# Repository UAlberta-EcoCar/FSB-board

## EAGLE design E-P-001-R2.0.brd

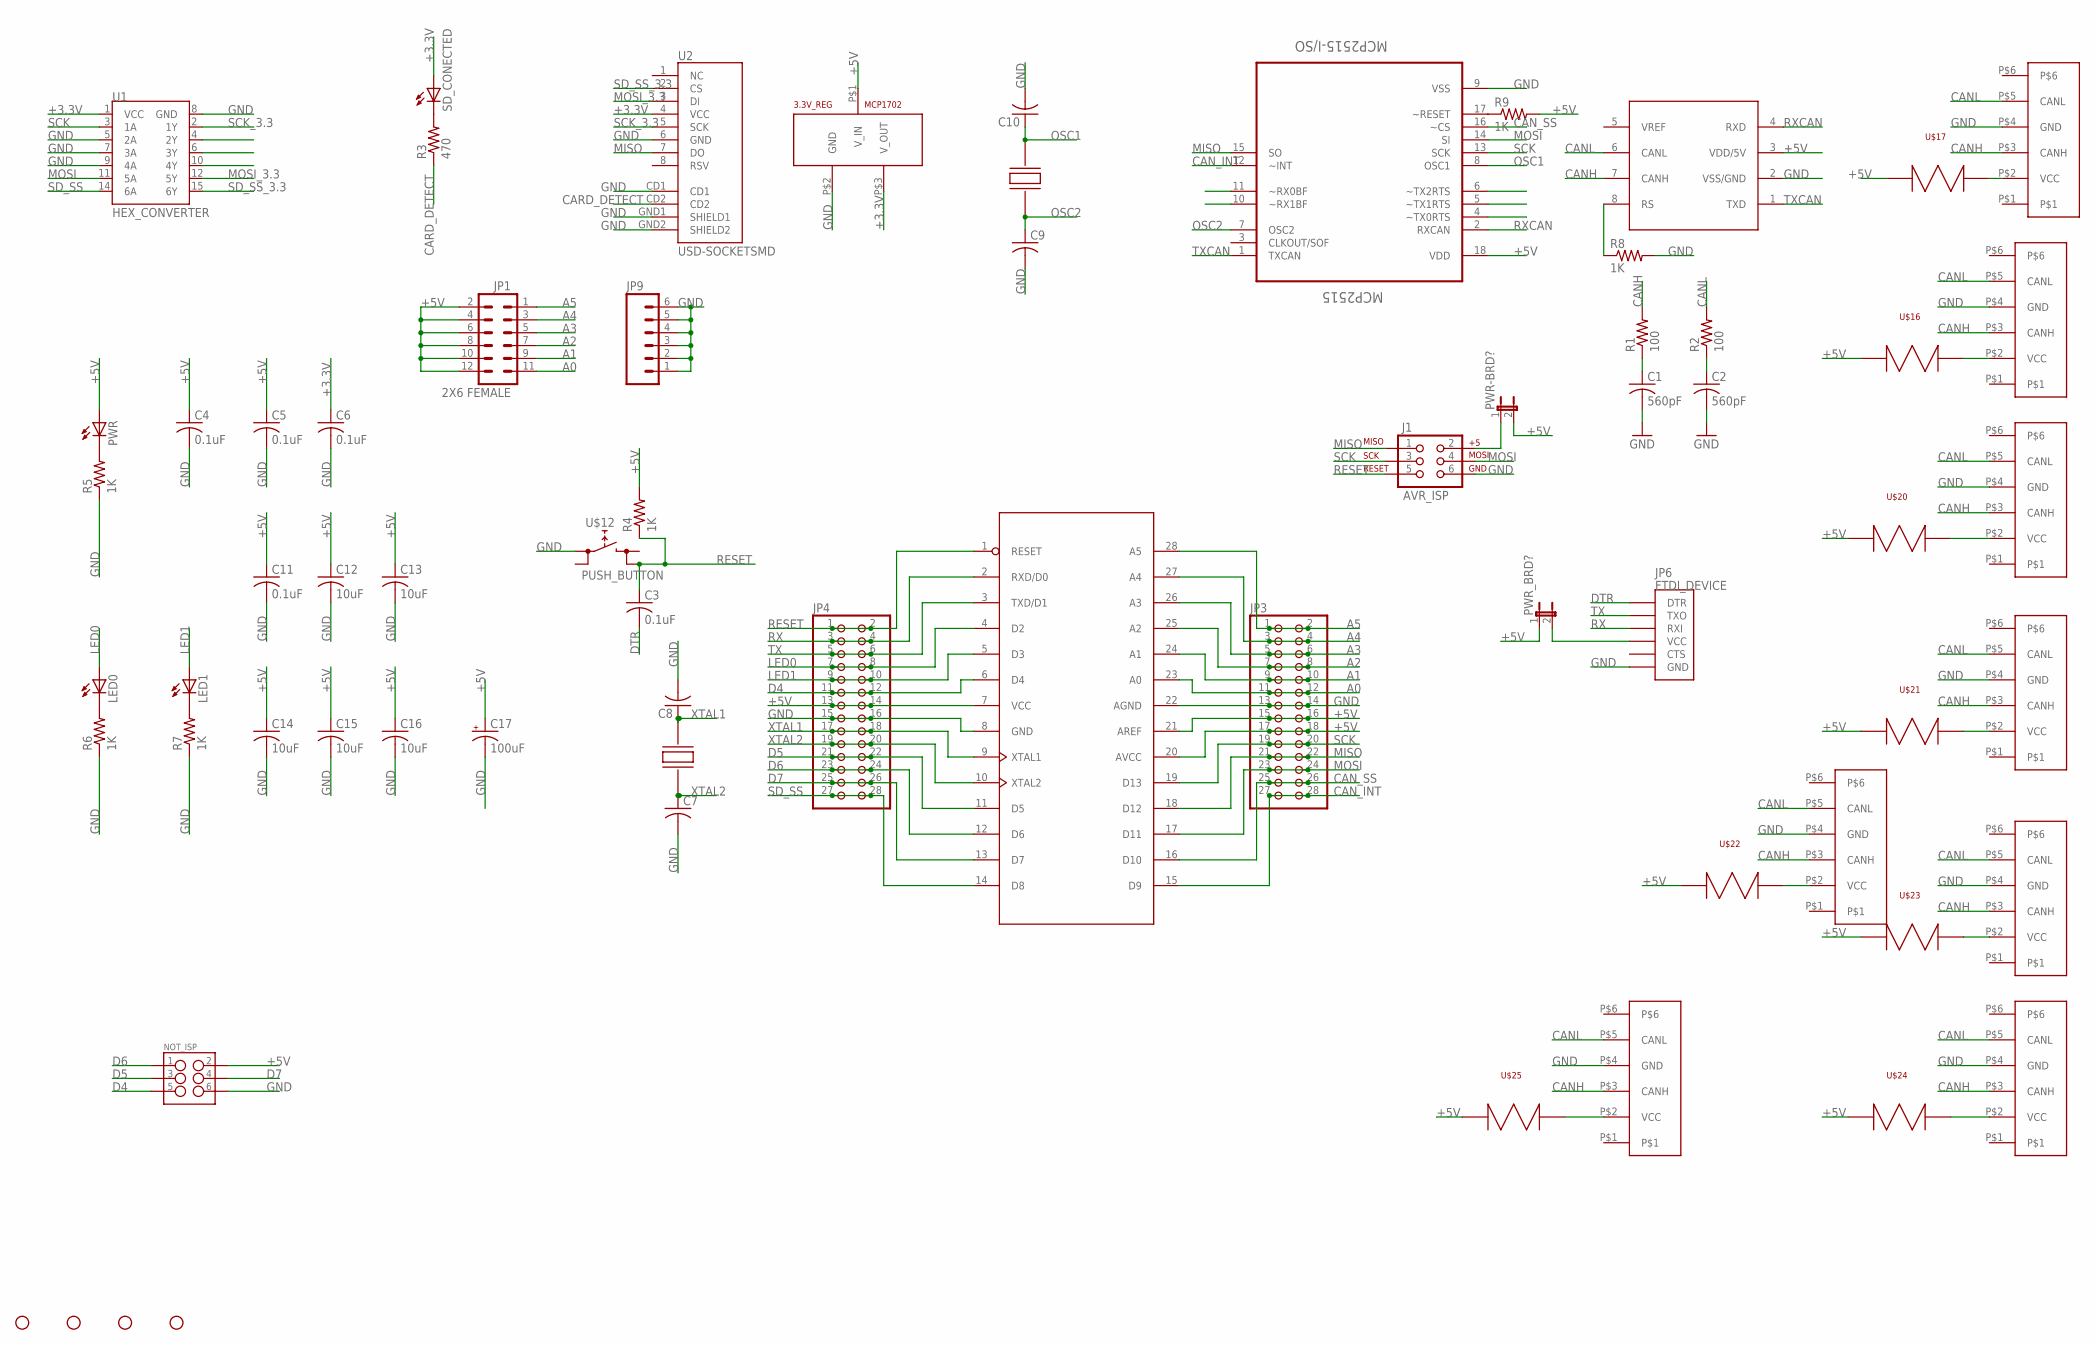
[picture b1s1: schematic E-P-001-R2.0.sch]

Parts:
3.3V_REG: MCP1702; SOT-23A
C1, C2: 560pF; C0805
C3, C4, C5, C6, C11: 0.1uF; C0805
C7, C8, C9, C10: C-USC0805; C0805
C12, C13, C14, C15, C16: 10uF; C0805
C17: 100uF; PANASONIC_D
J1: AVR_ISP; 2X3
JP1: 2X6 FEMALE; 2X6
JP3, JP4: PINHD-2X14; 2X14
JP6: FTDI_DEVICE; FTDI_DEVICE_SIDE
JP9: M06SILK_FEMALE_PTH; 1X06
LED0, LED1: LED1206; LED-1206
MCP2515: MCP2515-I/SO; SOIC127P1034X264-18N
NOT_ISP: M03X2FEMALE; 2X3
PWR: LED1206; LED-1206
PWR-BRD?: JP1E; JP1
PWR_BRD?: JP1E; JP1
R1, R2: 100; M0805
R3: 470; M0805
R4, R5, R6, R7, R8, R9: 1K; M0805
SD_CONECTED: LED1206; LED-1206
STANDOFF1, STANDOFF2, STANDOFF3, STANDOFF4: STAND-OFF
U1: HEX_CONVERTER; SO016
U2: USD-SOCKETSMD; MICRO-SD-SOCKET-PP
U$1, U$6, U$7, U$8, U$9, U$10, U$11, U$14: CAN_6P6C
U$2: MCP2551DIP; DIP8
U$4: ATMEGA328; DIP28-0.3IN
U$12: PUSH_BUTTON; PUSHBUTTON
U$16, U$17, U$20, U$21, U$22, U$23, U$24, U$25: FUSE; SM_MINI_AUTO-FUSE_HOLDER
U$18, U$19: CRYSTAL; 7A_CRYSTAL

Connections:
+3.3V: 3.3V_REG.P$3 (V_OUT), C6.1, SD_CONECTED.A, U1.1 (VCC), U2.4 (VCC)
+5V: 3.3V_REG.P$1 (V_IN), C4.1, C5.1, C11.1, C12.1, C13.1, C14.1, C15.1, C16.1, C17.+, JP1.2, JP1.4, JP1.6, JP1.8, JP1.10, JP1.12, JP3.15, JP3.16, JP3.17, JP3.18, JP4.13, JP4.14, MCP2515.18 (VDD), NOT_ISP.2, PWR.A, PWR-BRD?.2, PWR_BRD?.1, R4.2, R9.2, U$2.3 (VDD/5V), U$4.7 (VCC), U$4.20 (AVCC), U$4.21 (AREF), U$16.P$3, U$16.P$4, U$17.P$3, U$17.P$4, U$20.P$3, U$20.P$4, U$21.P$3, U$21.P$4, U$22.P$3, U$22.P$4, U$23.P$3, U$23.P$4, U$24.P$3, U$24.P$4, U$25.P$3, U$25.P$4
A0: JP1.11, JP3.11, JP3.12, U$4.23 (A0)
A1: JP1.9, JP3.9, JP3.10, U$4.24 (A1)
A2: JP1.7, JP3.7, JP3.8, U$4.25 (A2)
A3: JP1.5, JP3.5, JP3.6, U$4.26 (A3)
A4: JP1.3, JP3.3, JP3.4, U$4.27 (A4)
A5: JP1.1, JP3.1, JP3.2, U$4.28 (A5)
CANH: R1.2, U$1.P$3 (CANH), U$2.7 (CANH), U$6.P$3 (CANH), U$7.P$3 (CANH), U$8.P$3 (CANH), U$9.P$3 (CANH), U$10.P$3 (CANH), U$11.P$3 (CANH), U$14.P$3 (CANH)
CANL: R2.2, U$1.P$5 (CANL), U$2.6 (CANL), U$6.P$5 (CANL), U$7.P$5 (CANL), U$8.P$5 (CANL), U$9.P$5 (CANL), U$10.P$5 (CANL), U$11.P$5 (CANL), U$14.P$5 (CANL)
CAN_INT: JP3.27, JP3.28, MCP2515.12 (~INT), U$4.15 (D9)
CAN_SS: JP3.25, JP3.26, MCP2515.16 (~CS), U$4.16 (D10)
CARD_DETECT: R3.1, U2.CD2
D4: JP4.11, JP4.12, NOT_ISP.5, U$4.6 (D4)
D5: JP4.21, JP4.22, NOT_ISP.3, U$4.11 (D5)
D6: JP4.23, JP4.24, NOT_ISP.1, U$4.12 (D6)
D7: JP4.25, JP4.26, NOT_ISP.4, U$4.13 (D7)
DTR: C3.2, JP6.P$1 (DTR)
GND: 3.3V_REG.P$2 (GND), C1.2, C2.2, C4.2, C5.2, C6.2, C7.2, C8.2, C9.2, C10.2, C11.2, C12.2, C13.2, C14.2, C15.2, C16.2, C17.-, J1.6, JP3.13, JP3.14, JP4.15, JP4.16, JP6.P$6 (GND), JP9.1, JP9.2, JP9.3, JP9.4, JP9.5, JP9.6, MCP2515.9 (VSS), NOT_ISP.6, R5.1, R6.1, R7.1, R8.2, U1.5 (2A), U1.7 (3A), U1.8 (GND), U1.9 (4A), U2.6 (GND), U2.CD1, U2.GND1 (SHIELD1), U2.GND2 (SHIELD2), U$1.P$4 (GND), U$2.2 (VSS/GND), U$4.8 (GND), U$4.22 (AGND), U$6.P$4 (GND), U$7.P$4 (GND), U$8.P$4 (GND), U$9.P$4 (GND), U$10.P$4 (GND), U$11.P$4 (GND), U$12.L1 (L), U$14.P$4 (GND)
LED0: JP4.7, JP4.8, LED0.A, U$4.4 (D2)
LED1: JP4.9, JP4.10, LED1.A, U$4.5 (D3)
MISO: J1.1, JP3.21, JP3.22, MCP2515.15 (SO), U2.7 (DO), U$4.18 (D12)
MOSI: J1.4, JP3.23, JP3.24, MCP2515.14 (SI), U1.11 (5A), U$4.17 (D11)
MOSI_3.3: U1.12 (5Y), U2.3 (DI)
unnamed: U$14.P$2 (VCC), U$22.P$1, U$22.P$2
unnamed: U$11.P$2 (VCC), U$25.P$1, U$25.P$2
unnamed: R3.2, SD_CONECTED.C
unnamed: JP6.P$4 (VCC), PWR_BRD?.2
unnamed: LED0.C, R6.2
unnamed: LED1.C, R7.2
unnamed: R8.1, U$2.8 (RS)
unnamed: MCP2515.17 (~RESET), R9.1
unnamed: U$10.P$2 (VCC), U$24.P$1, U$24.P$2
unnamed: PWR.C, R5.2
unnamed: U$9.P$2 (VCC), U$23.P$1, U$23.P$2
unnamed: U$8.P$2 (VCC), U$21.P$1, U$21.P$2
unnamed: U$7.P$2 (VCC), U$20.P$1, U$20.P$2
unnamed: C1.1, R1.1
unnamed: C2.1, R2.1
unnamed: U$6.P$2 (VCC), U$16.P$1, U$16.P$2
unnamed: U$1.P$2 (VCC), U$17.P$1, U$17.P$2
unnamed: J1.2, PWR-BRD?.1
OSC1: C10.1, MCP2515.8 (OSC1), U$19.P$2
OSC2: C9.1, MCP2515.7 (OSC2), U$19.P$1
RESET: C3.1, J1.5, JP4.1, JP4.2, R4.1, U$4.1 (RESET), U$12.R2 (R)
RX: JP4.3, JP4.4, JP6.P$3 (RXI), U$4.2 (RXD/D0)
RXCAN: MCP2515.2 (RXCAN), U$2.4 (RXD)
SCK: J1.3, JP3.19, JP3.20, MCP2515.13 (SCK), U1.3 (1A), U$4.19 (D13)
SCK_3.3: U1.2 (1Y), U2.5 (SCK)
SD_SS: JP4.27, JP4.28, U1.14 (6A), U$4.14 (D8)
SD_SS_3.3: U1.15 (6Y), U2.2 (CS)
TX: JP4.5, JP4.6, JP6.P$2 (TXO), U$4.3 (TXD/D1)
TXCAN: MCP2515.1 (TXCAN), U$2.1 (TXD)
XTAL1: C8.1, JP4.17, JP4.18, U$4.9 (XTAL1), U$18.P$2
XTAL2: C7.1, JP4.19, JP4.20, U$4.10 (XTAL2), U$18.P$1

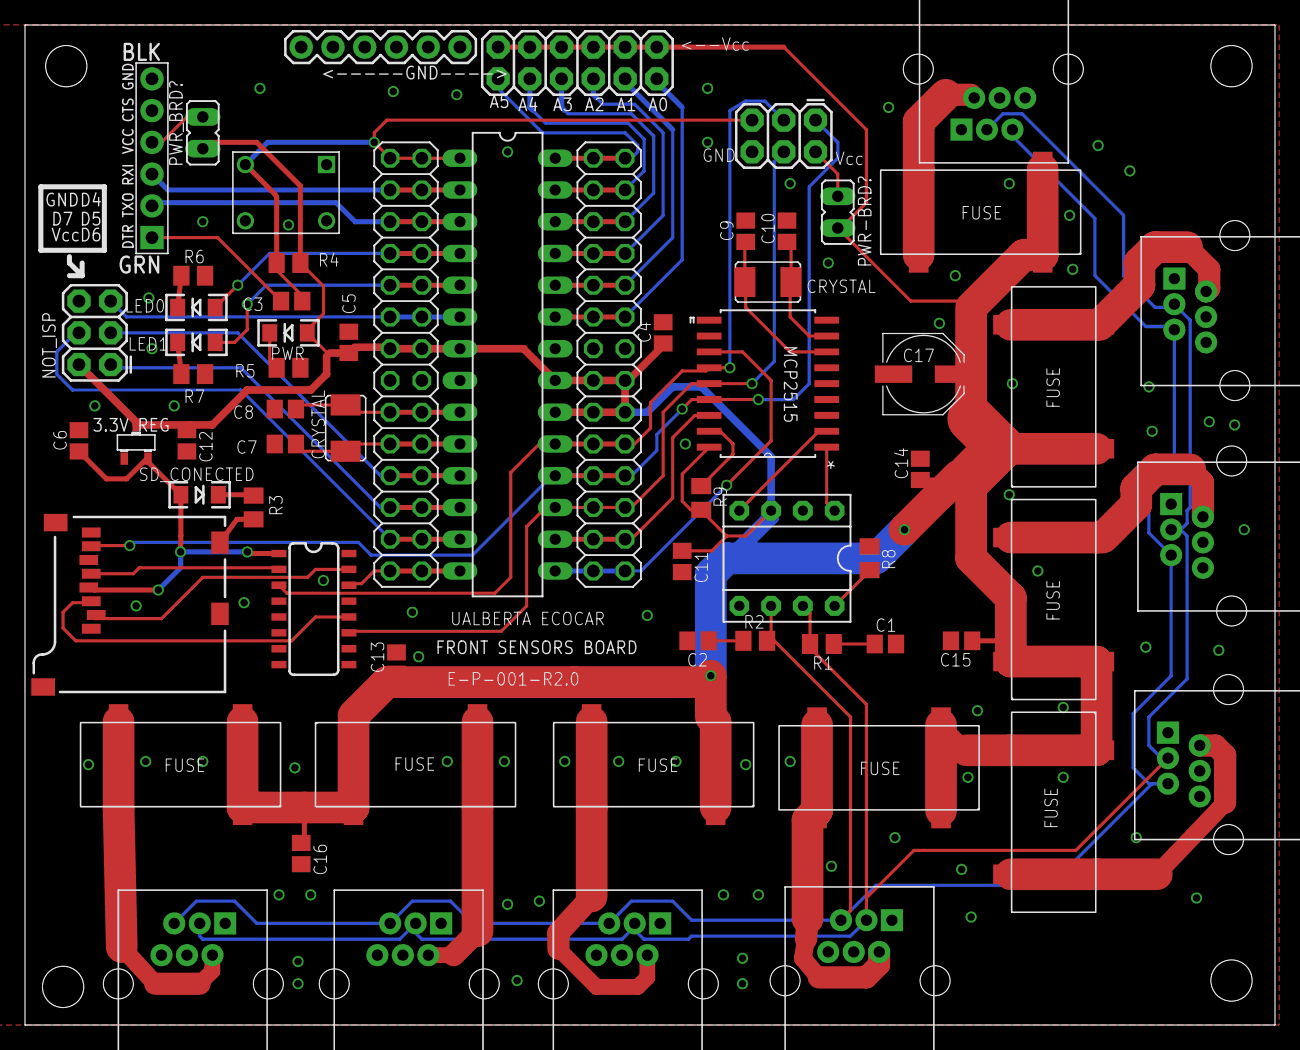
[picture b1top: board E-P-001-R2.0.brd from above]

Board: 2 copper layers, 100.0 x 80.0 mm, 68 parts (0 on the bottom side), 55 nets.

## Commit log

2016-01-23 added eagle files

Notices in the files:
parts and their libraries:
SparkFun-Connectors: Licensing: Creative Commons ShareAlike 4.0 International - https://creativecommons.org/licenses/by-sa/4.0
